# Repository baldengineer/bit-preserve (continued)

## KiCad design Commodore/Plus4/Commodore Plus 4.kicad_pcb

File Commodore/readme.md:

# Commodore
* VIC-20
  * [Assy 251027](https://github.com/baldengineer/bit-preserve/tree/master/Commodore/VIC-20)
* Plus4
  * [314001-04](https://github.com/baldengineer/bit-preserve/tree/master/Commodore/Plus4) (PCB 310162 Rev D)
* [C64](https://github.com/baldengineer/bit-preserve/tree/master/Commodore/C64)
  * [Schematic 251469](https://github.com/baldengineer/bit-preserve/tree/master/Commodore/C64/251469) (PCB 250425-01, 240441-01) 
* [C128](https://github.com/baldengineer/bit-preserve/tree/master/Commodore/C128)
  * [Assy 310378](https://github.com/baldengineer/bit-preserve/tree/master/Commodore/C128/310378)
* Peripherals
  * 1541 drive
    * [Assy 250446](https://github.com/baldengineer/bit-preserve/tree/master/Commodore/1541/250446)

# Wishlist
* PET
* C64
  * Schematic 326106 (PCB 326298-01)
  * Schematic 251022 (PCB KU-14194HB)
  * Schematic 251138 (PCB 250407-04)
* C64C
  * Schematic 252278 (PCB 250466)
  * Schematic 252312 (PCB 250469)
* C128D-CR
  * Schematic 252421 (PCB 250477-01)
* Peripherals
  * 1541-II drive

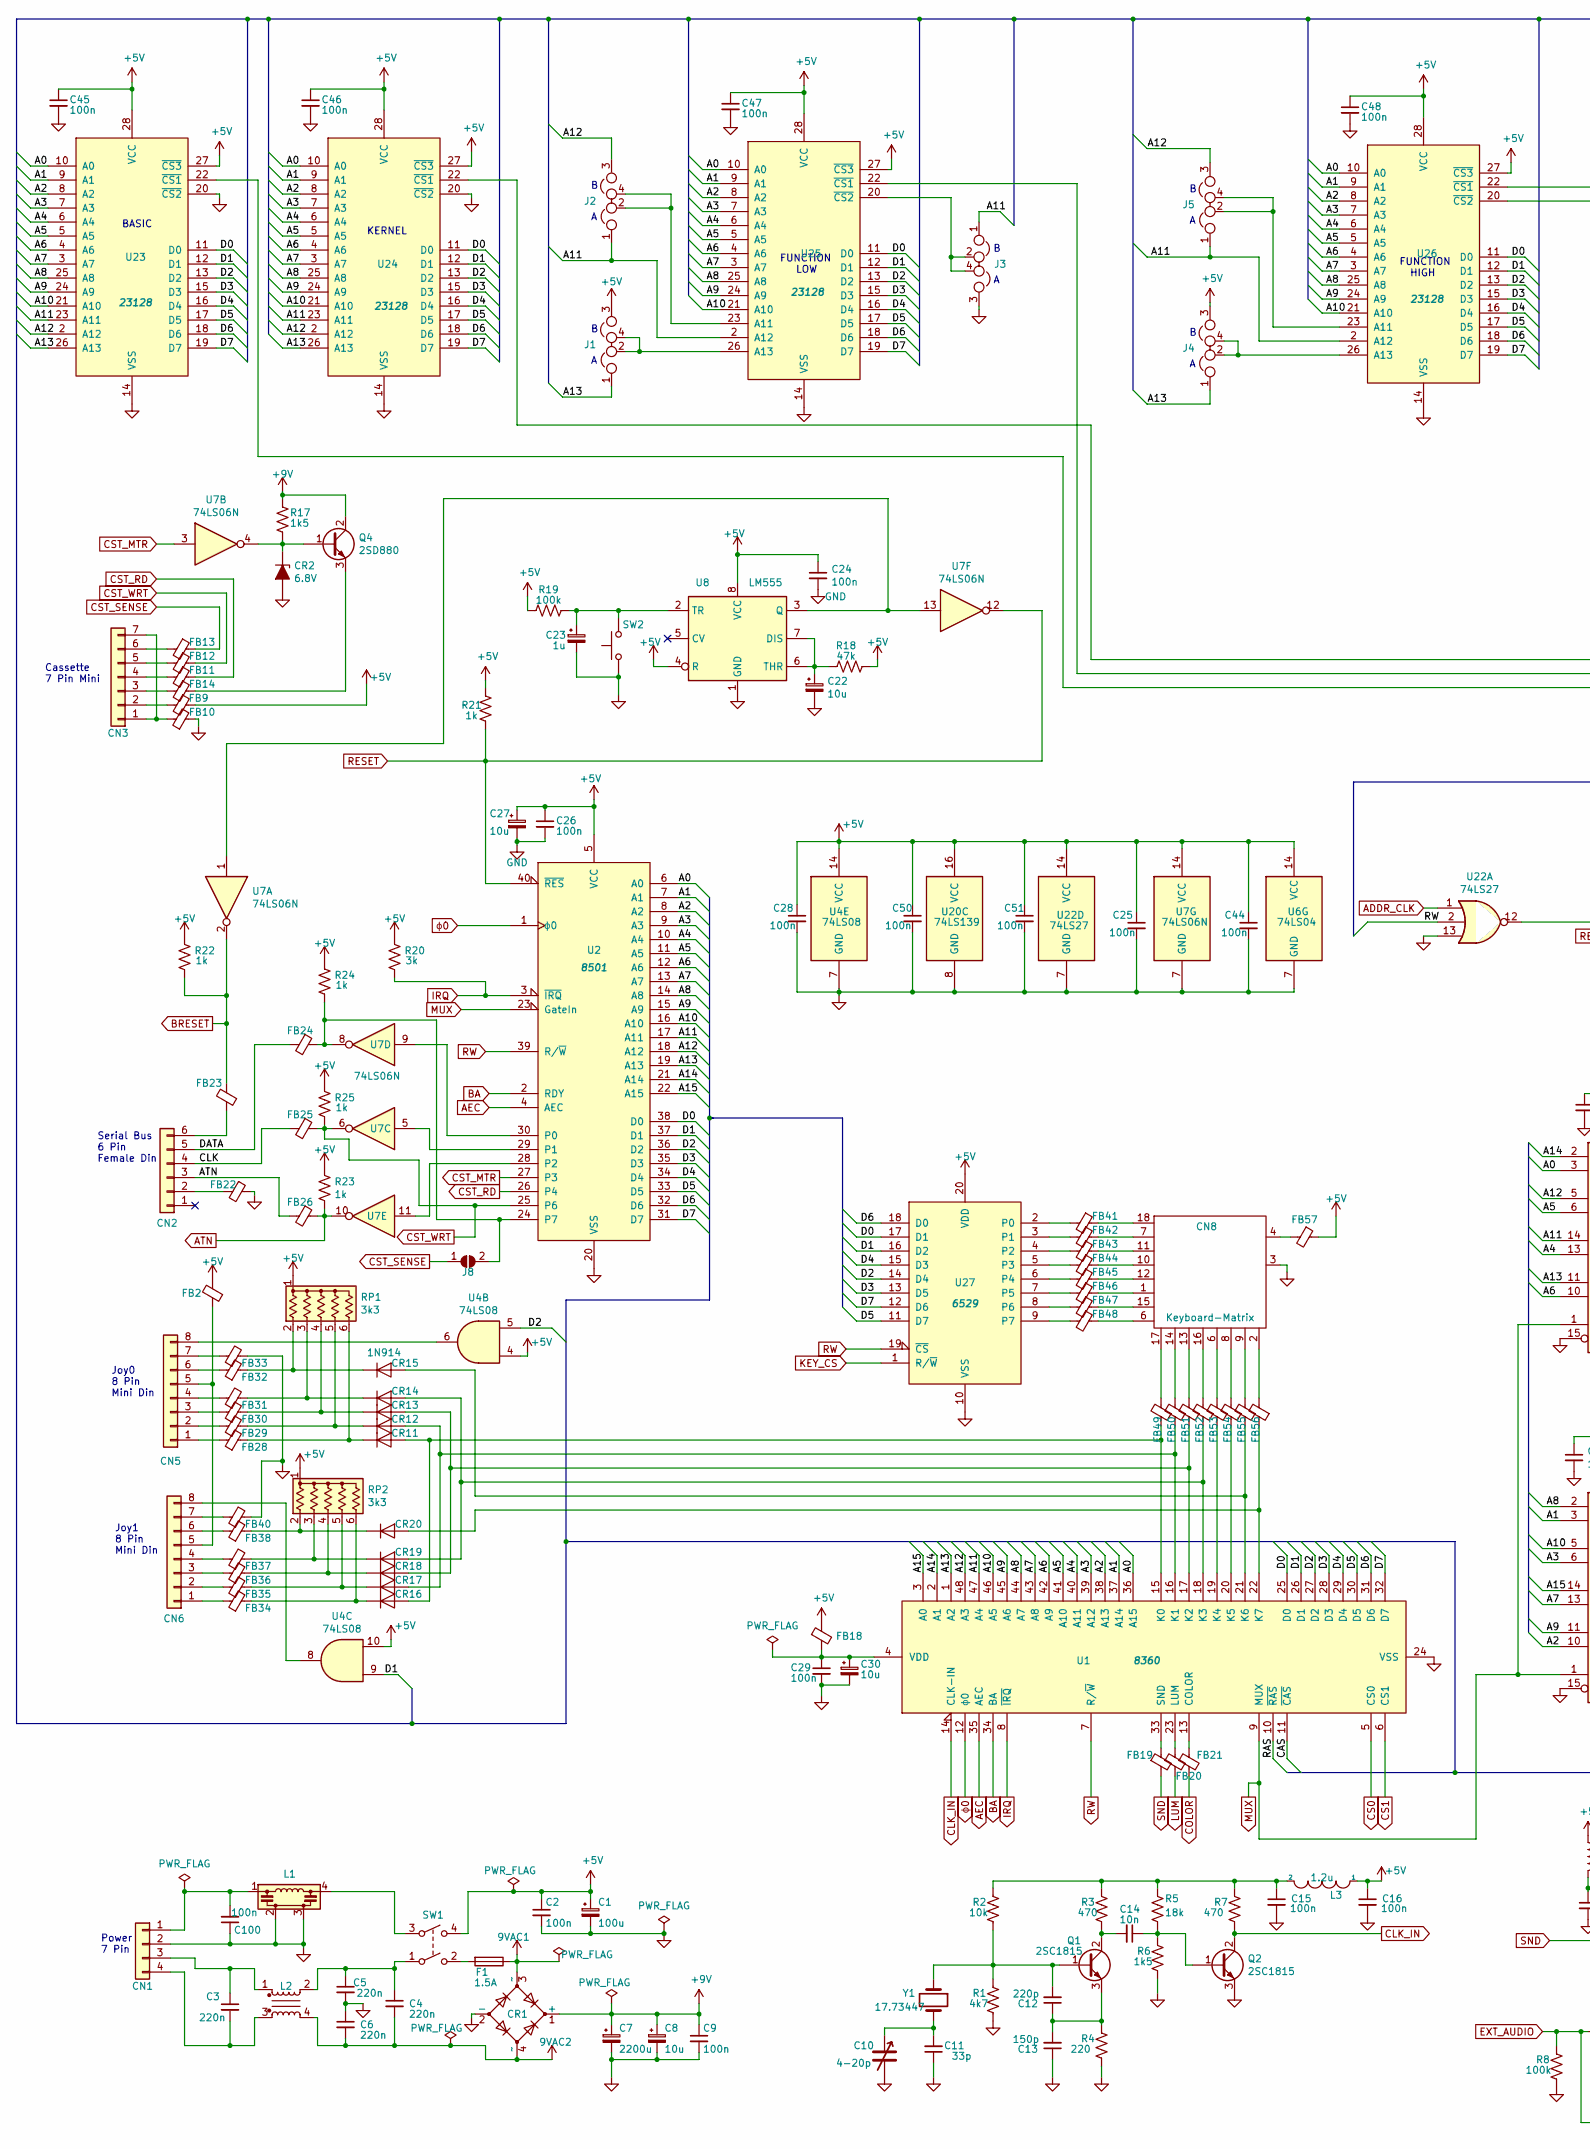
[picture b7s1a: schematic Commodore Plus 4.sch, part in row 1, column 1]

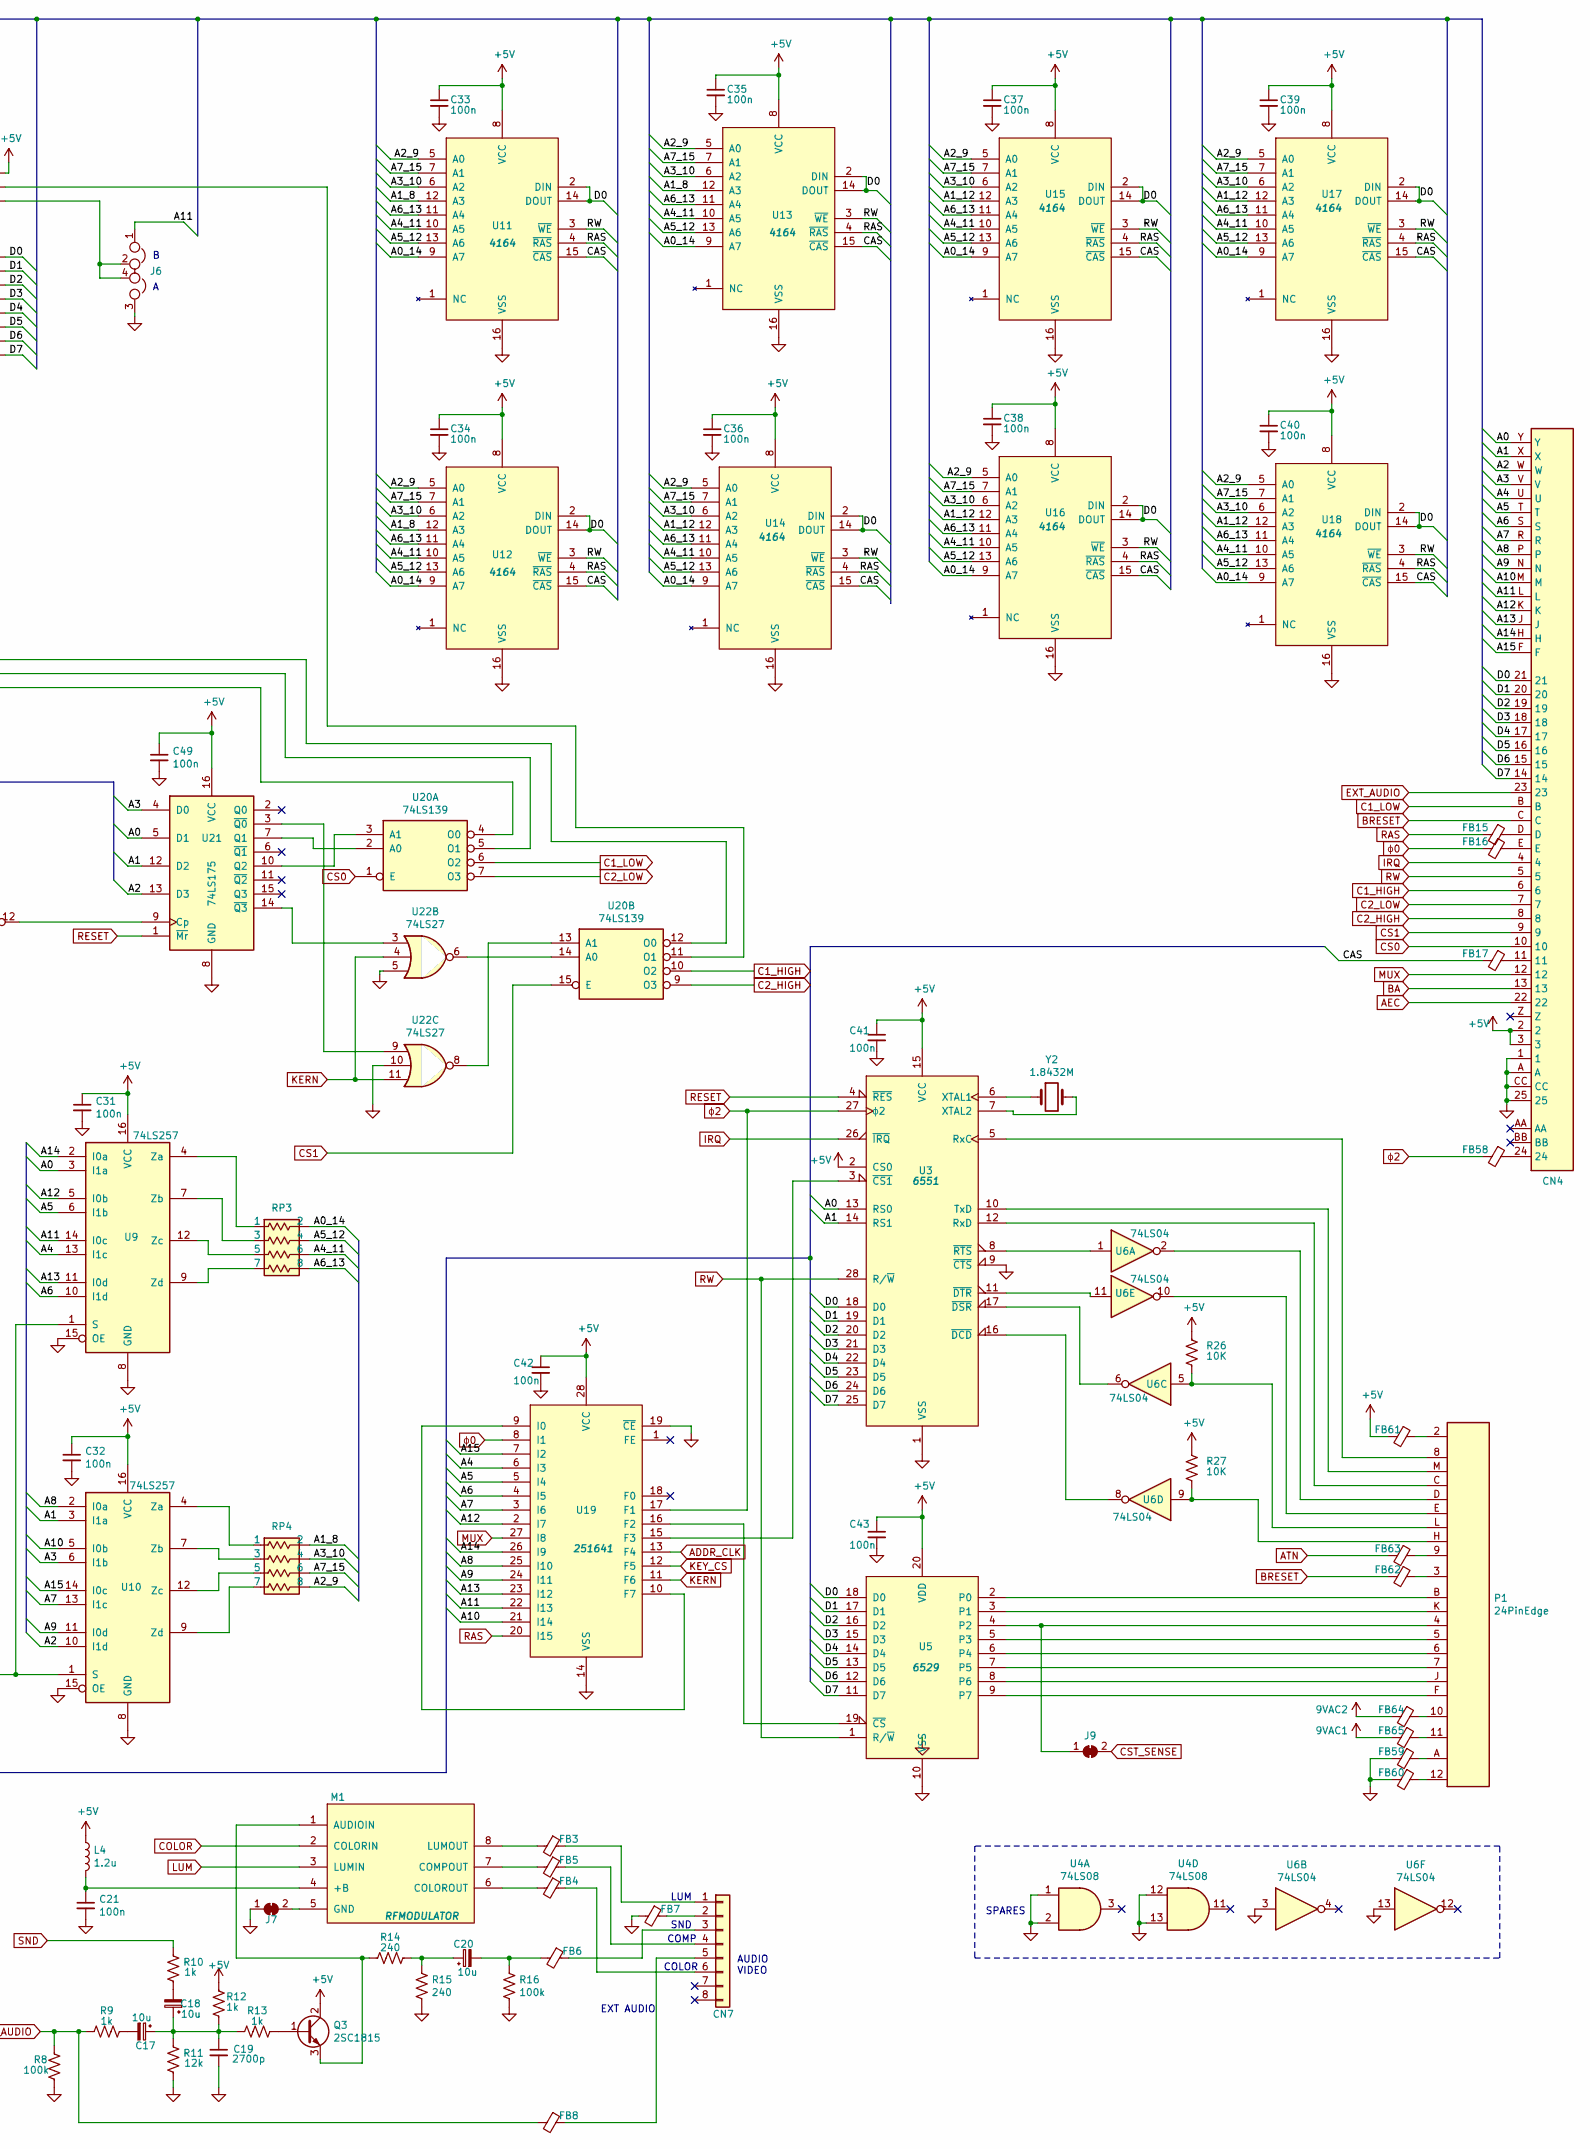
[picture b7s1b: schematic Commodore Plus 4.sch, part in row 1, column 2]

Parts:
C1: 100u; CP_Radial_D8.0mm_P3.50mm
C2, C9, C15, C16, C21, C24, C25, C26, C28, C29, C31, C32, C33, C34, C35, C36, C37, C38, C39, C41, C42, C43, C44, C45, C46, C47, C48, C49, C50, C51: 100n; C_Disc_D5.0mm_W2.5mm_P5.00mm
C3: 220n; C_Disc_D12.5mm_W5.0mm_P10.00mm
C4: 220n; Capacitor_D12.5mm_W5.0mm_P10.00mm
C5, C6: 220n; C_Disc_D5.0mm_W2.5mm_P5.00mm
C7: 2200u; CP_Axial_L40.0mm_D16.0mm_P48.00mm_Horizontal
C8, C20, C27: 10u; CP_Radial_D6.3mm_P2.50mm
C10: 4-20p; TrimCap_251029-02
C11: 33p; C_Disc_D5.0mm_W2.5mm_P5.00mm
C12: 220p; C_Disc_D5.0mm_W2.5mm_P5.00mm
C13: 150p; C_Disc_D5.0mm_W2.5mm_P5.00mm
C14: 10n; C_Disc_D5.0mm_W2.5mm_P5.00mm
C17, C18, C22, C30: 10u; C_Disc_10mm_6mm
C19: 2700p; C_Disc_D5.0mm_W2.5mm_P5.00mm
C23: 1u; CP_Radial_D6.3mm_P2.50mm
C40: 100n; C_Rect_L7.0mm_W2.5mm_P5.00mm
C100: 100n; C_Disc_D4.7mm_W2.5mm_P5.00mm
CN1: Conn_01x04; Connector_Power_4pin_251614_01
CN2: Conn_01x07; Connector_DIN_Female_6Pin_3rows
CN3: Conn_01x07; Connector_Mini-DIN_Female_7Pin_2rows
CN4: 50PinEdge; 50Pin_Edge_Connector
CN5, CN6: Conn_01x08; Connector_Mini-DIN_Female_8Pin_2rows
CN7: Conn_01x08; Connector_DIN_Female_8Pin_3rows
CN8: Keyboard-Matrix; Keyboard_Connector
CR1: D_Bridge_+-AA; Diode_Bridge_12.5x12.5
CR2: 6.8V; D_A-405_P12.70mm_Horizontal
CR11, CR12, CR13, CR14, CR15, CR16, CR17, CR18, CR19, CR20: 1N914; D_DO-35_SOD27_P12.70mm_Horizontal
F1: 1.5A; Fuseholder_Cylinder-6.3x32mm
FB2, FB3, FB4, FB5, FB6, FB7, FB8, FB9, FB10, FB11, FB12, FB13, FB14, FB22, FB23, FB24, FB25, FB26, FB28, FB29, FB30, FB31, FB32, FB33, FB34, FB35, FB36, FB37, FB38, FB40, FB59, FB61, FB62, FB63: Ferrite_Bead_Small; L_Axial_L7.0mm_D3.3mm_P5.08mm_Vertical
FB15, FB16, FB17, FB18, FB19, FB20, FB21, FB41, FB42, FB43, FB44, FB45, FB46, FB47, FB48, FB49, FB50, FB51, FB52, FB53, FB54, FB55, FB56, FB57, FB58, FB60, FB64, FB65: Ferrite_Bead_Small; Ferrite_Bead_L5.0mm_D3.6mm_P13.00mm_Horizontal
J1, J2, J3, J4, J5, J6: Jumper_NC_Dual; Jumper
J7, J9: SolderJumper_2_Bridged; SolderJumper-2_P1.3mm_Bridged_RoundedPad1.0x1.5mm
J8: SolderJumper_2_Open; SolderJumper-2_P1.3mm_Open_RoundedPad1.0x1.5mm
L1: EMI_Filter; EMI-Filter
L2: EMI_Filter_CommonMode; Noise_Filter
L3, L4: 1.2u; L_Axial_L10.0mm_D4.0mm_P15.5mm_Horizontal
M1: RFMODULATOR; RF_Modulator
P1: 24PinEdge; 24Pin_Edge
Q1, Q2, Q3: 2SC1815; TO-92L_Inline_Wide
Q4: 2SD880; TO-220-3_Vertical
R1: 4k7; Resistor_Horizontal
R2: 10k; Resistor_Horizontal
R3, R7: 470; Resistor_Horizontal
R4: 220; Resistor_Horizontal
R5: 18k; Resistor_Horizontal
R6, R17: 1k5; Resistor_Horizontal
R8, R16, R19: 100k; Resistor_Horizontal
R9, R10, R12, R13, R21, R22, R23, R24, R25: 1k; Resistor_Horizontal
R11: 12k; Resistor_Horizontal
R14, R15: 240; Resistor_Horizontal
R18: 47k; Resistor_Horizontal
R20: 3k; Resistor_Horizontal
R26, R27: 10K; Resistor_Horizontal
RP1, RP2: 3k3; R_Array_SIP6
RP3, RP4: Resistor-Network; R_Array_SIP8
SW1: SW_DPST; Switch-Rocker
SW2: SW_Push; Switch-Pushbutton
U1: 8360; DIP-48_W15.24mm
U2: 8501; DIP-40_W15.24mm
U3: 6551; DIP-28_W15.24mm
U4: 74LS08; DIP-14_W7.62mm
U5, U27: 6529; DIP-20_W7.62mm
U6: 74LS04; DIP-14_W7.62mm
U7: 74LS06N; DIP-14_W7.62mm
U8: LM555; DIP-8_W7.62mm
U9, U10: 74LS257; DIP-16_W7.62mm
U11, U12, U13, U14, U15, U16, U17, U18: 4164; DIP-16_W7.62mm
U19: 251641; DIP-28_W15.24mm
U20: 74LS139; DIP-16_W7.62mm
U21: 74LS175; DIP-16_W7.62mm
U22: 74LS27; DIP-14_W7.62mm
U23, U24, U25, U26: 23128; DIP-28_W15.24mm
Y1: 17.73447; Crystal_HC18-U_Horizontal
Y2: 1.8432M; Crystal_HC33-U_Horizontal

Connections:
9VAC1: CR1.3 (~~), F1.1, FB65.2
9VAC2: C4.2, C6.2, CR1.4 (~~), FB64.2, L2.4
+5V: C1.1, C2.1, C16.1, C24.1, C25.1, C26.1, C27.1, C28.1, C31.1, C32.1, C33.1, C34.1, C35.1, C36.1, C37.1, C38.1, C39.1, C40.1, C41.1, C42.1, C43.1, C44.1, C45.1, C46.1, C47.1, C48.1, C49.1, C50.1, C51.1, CN4.2, CN4.3, FB2.2, FB9.1, FB18.1, FB57.1, FB61.2, J1.3, J4.3, L3.1, L4.1, Q3.2 (C), R12.1, R18.1, R19.2, R20.1, R21.2, R22.1, R23.1, R24.1, R25.1, R26.1, R27.1, RP1.1 (common), RP2.1 (common), SW1.4, U2.5 (VCC), U3.2 (CS0), U3.15 (VCC), U4.4, U4.10, U4.14 (VCC), U5.20 (VDD), U6.14 (VCC), U7.14 (VCC), U8.4 (R), U8.8 (VCC), U9.16 (VCC), U10.16 (VCC), U11.8 (VCC), U12.8 (VCC), U13.8 (VCC), U14.8 (VCC), U15.8 (VCC), U16.8 (VCC), U17.8 (VCC), U18.8 (VCC), U19.28 (VCC), U20.16 (VCC), U21.16 (VCC), U22.14 (VCC), U23.27 (~CS3), U23.28 (VCC), U24.27 (~CS3), U24.28 (VCC), U25.27 (~CS3), U25.28 (VCC), U26.27 (~CS3), U26.28 (VCC), U27.20 (VDD)
+9V: C7.1, C8.1, C9.1, CR1.1 (+), Q4.2 (C), R17.1
/A0: CN4.Y, U1.36 (A15), U2.6 (A0), U3.13 (RS0), U9.3 (I1a), U21.5 (D1), U23.10 (A0), U24.10 (A0), U25.10 (A0), U26.10 (A0)
/A0_14: RP3.2, U11.9 (A7), U12.9 (A7), U13.9 (A7), U14.9 (A7), U15.9 (A7), U16.9 (A7), U17.9 (A7), U18.9 (A7)
/A1: CN4.X, U1.37 (A14), U2.7 (A1), U3.14 (RS1), U10.3 (I1a), U21.12 (D2), U23.9 (A1), U24.9 (A1), U25.9 (A1), U26.9 (A1)
/A1_8: RP4.2, U11.12 (A3), U12.12 (A3), U13.12 (A3)
/A1_12: U14.12 (A3), U15.12 (A3), U16.12 (A3), U17.12 (A3), U18.12 (A3)
/A2: CN4.W, U1.38 (A13), U2.8 (A2), U10.10 (I1d), U21.13 (D3), U23.8 (A2), U24.8 (A2), U25.8 (A2), U26.8 (A2)
/A2_9: RP4.8, U11.5 (A0), U12.5 (A0), U13.5 (A0), U14.5 (A0), U15.5 (A0), U16.5 (A0), U17.5 (A0), U18.5 (A0)
/A3: CN4.V, U1.39 (A12), U2.9 (A3), U10.6 (I1b), U21.4 (D0), U23.7 (A3), U24.7 (A3), U25.7 (A3), U26.7 (A3)
/A3_10: RP4.4, U11.6 (A2), U12.6 (A2), U13.6 (A2), U14.6 (A2), U15.6 (A2), U16.6 (A2), U17.6 (A2), U18.6 (A2)
/A4: CN4.U, U1.40 (A11), U2.10 (A4), U9.13 (I1c), U19.6 (I3), U23.6 (A4), U24.6 (A4), U25.6 (A4), U26.6 (A4)
/A4_11: RP3.6, U11.10 (A5), U12.10 (A5), U13.10 (A5), U14.10 (A5), U15.10 (A5), U16.10 (A5), U17.10 (A5), U18.10 (A5)
/A5: CN4.T, U1.41 (A10), U2.11 (A5), U9.6 (I1b), U19.5 (I4), U23.5 (A5), U24.5 (A5), U25.5 (A5), U26.5 (A5)
/A5_12: RP3.4, U11.13 (A6), U12.13 (A6), U13.13 (A6), U14.13 (A6), U15.13 (A6), U16.13 (A6), U17.13 (A6), U18.13 (A6)
/A6: CN4.S, U1.42 (A9), U2.12 (A6), U9.10 (I1d), U19.4 (I5), U23.4 (A6), U24.4 (A6), U25.4 (A6), U26.4 (A6)
/A6_13: RP3.8, U11.11 (A4), U12.11 (A4), U13.11 (A4), U14.11 (A4), U15.11 (A4), U16.11 (A4), U17.11 (A4), U18.11 (A4)
/A7: CN4.R, U1.43 (A8), U2.13 (A7), U10.13 (I1c), U19.3 (I6), U23.3 (A7), U24.3 (A7), U25.3 (A7), U26.3 (A7)
/A7_15: RP4.6, U11.7 (A1), U12.7 (A1), U13.7 (A1), U14.7 (A1), U15.7 (A1), U16.7 (A1), U17.7 (A1), U18.7 (A1)
/A8: CN4.P, U1.44 (A7), U2.14 (A8), U10.2 (I0a), U19.25 (I10), U23.25 (A8), U24.25 (A8), U25.25 (A8), U26.25 (A8)
/A9: CN4.N, U1.45 (A6), U2.15 (A9), U10.11 (I0d), U19.24 (I11), U23.24 (A9), U24.24 (A9), U25.24 (A9), U26.24 (A9)
/A10: CN4.M, U1.46 (A5), U2.16 (A10), U10.5 (I0b), U19.21 (I14), U23.21 (A10), U24.21 (A10), U25.21 (A10), U26.21 (A10)
/A11: CN4.L, J2.1, J3.1, J5.1, J6.1, U1.47 (A4), U2.17 (A11), U9.14 (I0c), U19.22 (I13), U23.23 (A11), U24.23 (A11), U25.2 (A12), U26.2 (A12)
/A12: CN4.K, J2.3, J5.3, U1.48 (A3), U2.18 (A12), U9.5 (I0b), U19.2 (I7), U23.2 (A12), U24.2 (A12)
/A13: CN4.J, J1.1, J4.1, U1.1 (A2), U2.19 (A13), U9.11 (I0d), U19.23 (I12), U23.26 (A13), U24.26 (A13)
/A14: CN4.H, U1.2 (A1), U2.21 (A14), U9.2 (I0a), U19.26 (I9)
/A15: CN4.F, U1.3 (A0), U2.22 (A15), U10.14 (I0c), U19.7 (I2)
/CAS: FB17.2, U1.11 (~CAS), U11.15 (~CAS), U12.15 (~CAS), U13.15 (~CAS), U14.15 (~CAS), U15.15 (~CAS), U16.15 (~CAS), U17.15 (~CAS), U18.15 (~CAS)
/CLK: CN2.4, FB25.2
/D0: CN4.21, U1.25 (D0), U2.38 (D0), U3.18 (D0), U5.18 (D0), U11.2 (DIN), U11.14 (DOUT), U12.2 (DIN), U12.14 (DOUT), U13.2 (DIN), U13.14 (DOUT), U14.2 (DIN), U14.14 (DOUT), U15.2 (DIN), U15.14 (DOUT), U16.2 (DIN), U16.14 (DOUT), U17.2 (DIN), U17.14 (DOUT), U18.2 (DIN), U18.14 (DOUT), U23.11 (D0), U24.11 (D0), U25.11 (D0), U26.11 (D0), U27.17 (D1)
/D1: CN4.20, U1.26 (D1), U2.37 (D1), U3.19 (D1), U4.9, U5.17 (D1), U23.12 (D1), U24.12 (D1), U25.12 (D1), U26.12 (D1), U27.16 (D2)
/D2: CN4.19, U1.27 (D2), U2.36 (D2), U3.20 (D2), U4.5, U5.16 (D2), U23.13 (D2), U24.13 (D2), U25.13 (D2), U26.13 (D2), U27.14 (D4)
/D3: CN4.18, U1.28 (D3), U2.35 (D3), U3.21 (D3), U5.15 (D3), U23.15 (D3), U24.15 (D3), U25.15 (D3), U26.15 (D3), U27.13 (D5)
/D4: CN4.17, U1.29 (D4), U2.34 (D4), U3.22 (D4), U5.14 (D4), U23.16 (D4), U24.16 (D4), U25.16 (D4), U26.16 (D4), U27.15 (D3)
/D5: CN4.16, U1.30 (D5), U2.33 (D5), U3.23 (D5), U5.13 (D5), U23.17 (D5), U24.17 (D5), U25.17 (D5), U26.17 (D5), U27.11 (D7)
/D6: CN4.15, U1.31 (D6), U2.32 (D6), U3.24 (D6), U5.12 (D6), U23.18 (D6), U24.18 (D6), U25.18 (D6), U26.18 (D6), U27.18 (D0)
/D7: CN4.14, U1.32 (D7), U2.31 (D7), U3.25 (D7), U5.11 (D7), U23.19 (D7), U24.19 (D7), U25.19 (D7), U26.19 (D7), U27.12 (D6)
/DATA: CN2.5, FB24.2
ADDR_CLK: U19.13 (F4), U22.1
AEC: CN4.22, U1.35 (AEC), U2.4 (AEC)
ATN: CN2.3, FB26.1, FB26.2, FB63.2, R23.2, U7.10
BA: CN4.13, U1.34 (BA), U2.2 (RDY)
BRESET: CN4.C, FB23.2, FB62.2, R22.2, U7.2
C1_HIGH: CN4.6, U20.10 (O2)
C1_LOW: CN4.B, U20.6 (O2)
C2_HIGH: CN4.8, U20.9 (O3)
C2_LOW: CN4.7, U20.7 (O3)
CLK_IN: Q2.2 (C), R7.2, U1.14 (CLK-IN)
COLOR: FB21.2, M1.2 (COLORIN)
CS0: CN4.10, U1.5 (CS0), U20.1 (E)
CS1: CN4.9, U1.6 (CS1), U20.15 (E)
CST_MTR: U2.27 (P3), U7.3
CST_RD: FB11.1, U2.26 (P4)
CST_SENSE: FB13.1, J8.1 (A), J9.2 (B)
CST_WRT: FB12.1, FB25.1, R25.2, U2.25 (P6), U7.6
EXT_AUDIO: CN4.23, FB8.2, R8.1, R9.2
GND: C1.2, C2.2, C5.2, C6.1, C7.2, C8.2, C9.2, C10.2, C11.1, C13.1, C15.2, C16.2, C19.2, C21.2, C22.2, C23.2, C24.2, C25.2, C26.2, C27.2, C28.2, C29.2, C30.2, C31.2, C32.2, C33.2, C34.2, C35.2, C36.2, C37.2, C38.2, C39.2, C40.2, C41.2, C42.2, C43.2, C44.2, C45.2, C46.2, C47.2, C48.2, C49.2, C50.2, C51.2, C100.1, CN1.2, CN4.1, CN4.25, CN4.A, CN4.CC, CN8.3, CR1.2 (-), CR2.2 (A), FB7.2, FB10.2, FB22.1, FB33.2, FB40.2, FB59.2, FB60.2, J3.3, J6.3, J7.1 (A), L1.2, L1.3, Q2.3 (E), R1.2, R4.2, R6.2, R8.2, R11.2, R15.2, R16.2, SW2.1, U1.24 (VSS), U2.20 (VSS), U3.1 (VSS), U3.9 (~CTS), U4.1, U4.2, U4.7 (GND), U4.12, U4.13, U5.10 (VSS), U6.3, U6.7 (GND), U6.13, U7.7 (GND), U8.1 (GND), U9.8 (GND), U9.15 (OE), U10.8 (GND), U10.15 (OE), U11.16 (VSS), U12.16 (VSS), U13.16 (VSS), U14.16 (VSS), U15.16 (VSS), U16.16 (VSS), U17.16 (VSS), U18.16 (VSS), U19.14 (VSS), U19.19 (~CE), U20.8 (GND), U21.8 (GND), U22.5, U22.7 (GND), U22.10, U22.13, U23.14 (VSS), U23.20 (~CS2), U24.14 (VSS), U24.20 (~CS2), U25.14 (VSS), U26.14 (VSS), U27.10 (VSS)
IRQ: CN4.4, R20.2, U1.8 (~IRQ), U2.3 (~IRQ), U3.26 (~IRQ)
KERN: U19.11 (F6), U22.4, U22.11
KEY_CS: U19.12 (F5), U27.1 (R/~W)
LUM: FB20.2, M1.3 (LUMIN)
MUX: CN4.12, U1.9 (MUX), U2.23 (GateIn), U9.1 (S), U10.1 (S), U19.27 (I8)
unnamed: C3.1, CN1.3, L2.1
unnamed: C3.2, CN1.4, L2.3
unnamed: C4.1, C5.1, L2.2, SW1.1
unnamed: C10.1, C11.2, Y1.2
unnamed: C12.1, C13.2, Q1.3 (E), R4.1
unnamed: C12.2, Q1.1 (B), R1.1, R2.2, Y1.1
unnamed: C14.1, Q2.1 (B), R5.2, R6.1
unnamed: C14.2, Q1.2 (C), R3.2
unnamed: C15.1, L3.2, R2.1, R3.1, R5.1, R7.1
unnamed: C17.1, C18.1, C19.1, R11.1, R12.2, R13.2
unnamed: C17.2, R9.1
unnamed: C18.2, R10.2
unnamed: C20.1, R14.1, R15.1
unnamed: C20.2, FB6.2, R16.1
unnamed: C21.1, L4.2, M1.4 (+B)
unnamed: C22.1, R18.2, U8.6 (THR), U8.7 (DIS)
unnamed: C23.1, R19.1, SW2.2, U8.2 (TR)
unnamed: C29.1, C30.1, FB18.2, U1.4 (VDD)
unnamed: C100.2, CN1.1, L1.1
unnamed: CN2.2, FB22.2
unnamed: CN2.6, FB23.1
unnamed: CN3.1, CN3.7, FB10.1
unnamed: CN3.2, FB9.2
unnamed: CN3.3, FB14.2
unnamed: CN3.4, FB11.2
unnamed: CN3.5, FB12.2
unnamed: CN3.6, FB13.2
unnamed: CN4.11, FB17.1
unnamed: CN4.24, FB58.1
unnamed: CN4.D, FB15.1
unnamed: CN4.E, FB16.1
unnamed: CN5.1, FB28.1
unnamed: CN5.2, FB29.1
unnamed: CN5.3, FB30.1
unnamed: CN5.4, FB31.1
unnamed: CN5.5, CN6.5, FB2.1
unnamed: CN5.6, FB32.1
unnamed: CN5.7, FB33.1
unnamed: CN5.8, U4.6
unnamed: CN6.1, FB34.1
unnamed: CN6.2, FB35.1
unnamed: CN6.3, FB36.1
unnamed: CN6.4, FB37.1
unnamed: CN6.6, FB38.1
unnamed: CN6.7, FB40.1
unnamed: CN6.8, U4.8
unnamed: CN7.1, FB3.1
unnamed: CN7.2, FB7.1
unnamed: CN7.3, FB6.1
unnamed: CN7.4, FB5.1
unnamed: CN7.5, FB8.1
unnamed: CN7.6, FB4.1
unnamed: CN8.1, FB46.1
unnamed: CN8.2, FB56.2
unnamed: CN8.4, FB57.2
unnamed: CN8.7, FB42.1
unnamed: CN8.8, FB54.2
unnamed: CN8.9, FB55.2
unnamed: CN8.10, FB44.1
unnamed: CN8.11, FB43.1
unnamed: CN8.12, FB45.1
unnamed: CN8.13, FB51.2
unnamed: CN8.14, FB50.2
unnamed: CN8.15, FB47.1
unnamed: CN8.16, FB52.2
unnamed: CN8.17, FB49.2
unnamed: CN8.18, FB41.1
unnamed: CR2.1 (K), Q4.1 (B), R17.2, U7.4
unnamed: CR11.1 (K), FB28.2, RP1.6 (R5)
unnamed: CR11.2 (A), CR16.2 (A), FB49.1, U1.15 (K0)
unnamed: CR12.1 (K), FB29.2, RP1.5 (R4)
unnamed: CR12.2 (A), CR17.2 (A), FB50.1, U1.16 (K1)
unnamed: CR13.1 (K), FB30.2, RP1.4 (R3)
unnamed: CR13.2 (A), CR18.2 (A), FB51.1, U1.17 (K2)
unnamed: CR14.1 (K), FB31.2, RP1.3 (R2)
unnamed: CR14.2 (A), CR19.2 (A), FB52.1, U1.18 (K3)
unnamed: CR15.1 (K), FB32.2, RP1.2 (R1)
unnamed: CR15.2 (A), FB55.1, U1.21 (K6)
unnamed: CR16.1 (K), FB34.2, RP2.6 (R5)
unnamed: CR17.1 (K), FB35.2, RP2.5 (R4)
unnamed: CR18.1 (K), FB36.2, RP2.4 (R3)
unnamed: CR19.1 (K), FB37.2, RP2.3 (R2)
unnamed: CR20.1 (K), FB38.2, RP2.2 (R1)
unnamed: CR20.2 (A), FB56.1, U1.22 (K7)
unnamed: F1.2, SW1.2
unnamed: FB3.2, M1.8 (LUMOUT)
unnamed: FB4.2, M1.6 (COLOROUT)
unnamed: FB5.2, M1.7 (COMPOUT)
unnamed: FB14.1, Q4.3 (E)
unnamed: FB19.1, U1.33 (SND)
unnamed: FB20.1, U1.23 (LUM)
unnamed: FB21.1, U1.13 (COLOR)
unnamed: FB24.1, J8.2 (B), R24.2, U2.24 (P7), U7.8
unnamed: FB41.2, U27.2 (P0)
unnamed: FB42.2, U27.3 (P1)
unnamed: FB43.2, U27.4 (P2)
unnamed: FB44.2, U27.5 (P3)
unnamed: FB45.2, U27.6 (P4)
unnamed: FB46.2, U27.7 (P5)
unnamed: FB47.2, U27.8 (P6)
unnamed: FB48.2, U27.9 (P7)
unnamed: FB53.1, U1.19 (K4)
unnamed: FB54.1, U1.20 (K5)
unnamed: FB59.1, P1.A
unnamed: FB60.1, P1.12
unnamed: FB61.1, P1.2
unnamed: FB62.1, P1.3
unnamed: FB63.1, P1.9
unnamed: FB64.1, P1.10
unnamed: FB65.1, P1.11
unnamed: J1.2, J1.4, U25.26 (A13)
unnamed: J2.2, J2.4, U25.23 (A11)
unnamed: J3.2, J3.4, U25.20 (~CS2)
unnamed: J4.2, J4.4, U26.26 (A13)
unnamed: J5.2, J5.4, U26.23 (A11)
unnamed: J6.2, J6.4, U26.20 (~CS2)
unnamed: J7.2 (B), M1.5 (GND)
unnamed: J9.1 (A), P1.4, U5.4 (P2)
unnamed: L1.4, SW1.3
unnamed: M1.1 (AUDIOIN), Q3.3 (E), R14.2
unnamed: P1.5, U5.5 (P3)
unnamed: P1.6, U5.6 (P4)
unnamed: P1.7, U5.7 (P5)
unnamed: P1.8, U3.5 (RxC)
unnamed: P1.B, U5.2 (P0)
unnamed: P1.C, U3.12 (RxD)
unnamed: P1.D, U6.2
unnamed: P1.E, U6.10
unnamed: P1.F, U5.9 (P7)
unnamed: P1.H, R27.2, U6.9
unnamed: P1.J, U5.8 (P6)
unnamed: P1.K, U5.3 (P1)
unnamed: P1.L, R26.2, U6.5
unnamed: P1.M, U3.10 (TxD)
unnamed: Q3.1 (B), R13.1
unnamed: RP3.1, U9.4 (Za)
unnamed: RP3.3, U9.7 (Zb)
unnamed: RP3.5, U9.12 (Zc)
unnamed: RP3.7, U9.9 (Zd)
unnamed: RP4.1, U10.4 (Za)
unnamed: RP4.3, U10.7 (Zb)
unnamed: RP4.5, U10.12 (Zc)
unnamed: RP4.7, U10.9 (Zd)
unnamed: U2.28 (P2), U7.11
unnamed: U2.29 (P1), U7.5
unnamed: U2.30 (P0), U7.9
unnamed: U3.6 (XTAL1), Y2.1
unnamed: U3.7 (XTAL2), Y2.2
unnamed: U3.8 (~RTS), U6.1
unnamed: U3.11 (~DTR), U6.11
unnamed: U3.16 (~DCD), U6.8
unnamed: U3.17 (~DSR), U6.6
unnamed: U7.1, U7.13, U8.3 (Q)
unnamed: U19.9 (I0), U19.10 (F7)
unnamed: U3.3 (~CS1), U19.15 (F3)
unnamed: U5.19 (~CS), U19.16 (F2)
unnamed: U20.2 (A0), U21.7 (Q1)
unnamed: U20.3 (A1), U21.10 (Q2)
unnamed: U20.4 (O0), U23.22 (~CS1)
unnamed: U20.5 (O1), U25.22 (~CS1)
unnamed: U20.11 (O1), U26.22 (~CS1)
unnamed: U20.12 (O0), U24.22 (~CS1)
unnamed: U20.13 (A1), U22.8
unnamed: U20.14 (A0), U22.6
unnamed: U21.3 (~Q0), U22.9
unnamed: U21.9 (Cp), U22.12
unnamed: U21.14 (~Q3), U22.3
RAS: FB15.2, U1.10 (~RAS), U11.4 (~RAS), U12.4 (~RAS), U13.4 (~RAS), U14.4 (~RAS), U15.4 (~RAS), U16.4 (~RAS), U17.4 (~RAS), U18.4 (~RAS), U19.20 (I15)
RESET: R21.1, U2.40 (~RES), U3.4 (~RES), U7.12, U21.1 (~Mr)
RW: CN4.5, U1.7 (R/~W), U2.39 (R/~W), U3.28 (R/~W), U5.1 (R/~W), U11.3 (~WE), U12.3 (~WE), U13.3 (~WE), U14.3 (~WE), U15.3 (~WE), U16.3 (~WE), U17.3 (~WE), U18.3 (~WE), U22.2, U27.19 (~CS)
SND: FB19.2, R10.1
ϕ0: FB16.2, U1.12 (ϕ0), U2.1 (ϕ0), U19.8 (I1)
ϕ2: FB58.2, U3.27 (ϕ2), U19.17 (F1)

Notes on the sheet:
BASIC
KERNEL
FUNCTION LOW
FUNCTION HIGH
Power 7 Pin
Serial Bus 6 Pin Female Din
Joy0 8 Pin Mini Din
Joy1 8 Pin Mini Din
LUM
SND
COMP
EXT AUDIO
COLOR
Cassette 7 Pin Mini
AUDIO VIDEO
SPARES

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
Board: 2 copper layers, 216 parts (0 on the bottom side), 238 nets, no tracks yet.

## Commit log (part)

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2019-08-05 Added value to clock trimcap
2019-08-05 Checked all stand-alone board resistors (except on RF modulator) in BOM against Service Manual parts list, and added rating and tolerance information from parts list to them - noted the following Rs 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
2019-08-06 Showing Power LED connection to LED connector
2019-08-07 added .gitignore for -bak files generated by Kicad
2019-08-07 checked all inductors (except RF mod.) in KiCad schematic BOM against Service Manual Parts List
2019-08-09 checked all diaodes (except in RF mod.) in KiCad schematic BOM against Service Manual parts list
2019-08-09 Added missing pull-ups on /EXROM and /GAME in cartridge expansion section (part of missing RP4 resistor network)
2019-08-09 Added missing R51 pull-up on R/W in cartridge expansion section
2019-08-09 checked SW1 abd F1 in KiCad schematic BOM against Service Manual parts list
2019-08-10 schematic revision/issue-date bump to 0.2/2019-08-11
2019-08-11 refac: Moved RP4 out of IO section to top-level sheet, as it's not really IO specific. Also fixed a bus connectivity issue with RP4 reported by ERC
2019-08-11 Replaced sym-lib-table absolute paths from initial submitter's file system with project relative paths, so that libs can be found when schematic is opened from other people's working copies
2019-08-13 Some part of the Terminal Section has been redrawn, no netlist changes
2019-09-24 Add Subfolder for computers by Dragon Data Ltd.
    Add basic KiCad project files for Dragon 32 computer
2019-09-27 Add MC6883/74LS783 chip
2019-09-27 Fix pin assginment on 74LS783/MC6883
2019-09-27 Add Dragon 32 BASIC ROM
2019-09-27 Add MC6847 symbol
2019-09-27 Fix GND assignment
2019-09-27 Add Siemens RAM Memory library
2020-01-01 Updated part names
2020-01-01 Added Decoupling Capacitor Page
    Need to verify.
2020-03-13 Schematics for Amiga A500 Power Supply
2020-04-19 Add C64B3 schematic
    This adds C= scheamtic #252278 which matches PCB #250466.
    It also adds TMS RAM 4464 in three speed version.
    MOS 8701 is updated to make pin 4 not hidden as it's
    usually connected to ground, not left floating.
2020-04-19 clarifying which number is used: assembly or board
2020-05-14 Captured digital/ICs for Sound page
    During live stream, captured the ICs on the sound page. Other page updates just because I opened the files to check status of the project.
2020-06-07 Video page
    Updated a few schematic symbols
2020-06-09 Adding CC-BY-SA License
2020-06-18 Worked on IWM Page
    Almost done with it! Thanks Stream!
2020-06-25 Finish IWM-4 Woo Hoo!
2020-07-19 Finished Sound Page (and the rest!)
    Cleaned up Capacitor page with polarized caps.
    Stil need to make some global labels (optional)
    Thank you chat! -> 2020-07-19
2020-08-22 Update readme.md
    Fixed formatting
2020-08-23 Started work on power supply
2020-08-25 Add CPU, video
2020-08-26 Complete video schematic
2020-10-14 Finish drawing initial version of Coco2 schematic
2020-10-15 Update Memory_Controller_Motorola.lib
    Change pin R/~W on MC6883 from output to input
2020-12-26 Fix CS1 signal on VIA1
2020-12-28 Pass 1 top row
    something weird happen, save me
2020-12-31 Horz, Vert, and PS ICs
    Streamed 2020-12-31
2021-01-03 Finish Schematic
2021-01-10 oops.
    Forgot to save when I committed.
2021-01-26 shematics for cpu, rom, io decode sheets halfway thru
2021-01-30 Updated RAM and RAM select sheets
2021-01-31 Added clock generator sheet, halfway thru it
2021-02-06 Update readme.md
    Added Apple II+ activity status.
2021-02-07 Additional updated to the Clock Generator Sheet, and the CPU sheet
2021-02-13 Added the CPU schematic
2021-02-14 Added video generation sheet
2021-02-15 Started to add footprints and vendor part numbers for BOM creation ordering ect... Started putting together power section.
2021-02-16 fixed the direction on some of the heirarichal pins
2021-02-18 -copied librares from troysbucket trs80 design and modified them -added DRAM schematic -started to put together SAM schematic.
2021-02-20 -Finished SAM sheet -Finsihed DRAM sheet
2021-02-21 added J6 connector ans started adding the video and periperals sheet
2021-02-21 Created separate II and II+ projects, stated updating the II+
2021-02-22 Updated Readme.md with more sources
2021-03-10 Schematic for BBC Micro PSU
2021-03-23 Added some more stuff to the perhipherals sheet
2021-03-23 Finished peripherals sheet. I think......
2021-03-24 -Finished schematic. -Cleaned up schematic. -Added final footprint. -Started PCB
2021-03-25 Fixed some footprints that had wrong number of pins.
2021-03-27 -Added more 3 models. -Improved alignment on some of the components.
2021-04-12 fixed unconnected traces
2021-04-13 added interactive BOM
2021-04-18 -added no fill zone around q1 -added part number for u4 pin socket -changed part number for c11 -modifed footprint for c43 -fixed value for c62 in schematic
2021-04-18 removed wayward no-connect
2021-04-20 added a revision number to the schematic and the pcb
2021-04-23 added Bill Of Materials BOM
2021-04-25 -cleaned up fab layer to display compoent values -updated gerbers and iBOM
2021-04-29 fixed 3d-model for din4 connector
2021-04-30 -Shortened the board by 1.5mm from the left side. -This should be the last change!!!
2021-05-03 added ground pads under cardedge connector
2021-05-11 added two more 3d models
2021-05-14 fixing amiga deleted file
2021-05-17 Clean-up after detailed circuit analysis - Fixed Reference to library in project file - Fixed BABUS tags on HCT245 (had wrong nets) - Flipped HCT245 circuits on MEGAII page to better match In/Out flo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
2021-06-03 Add page 1 schematic symbols
2021-06-04 Add page 2 symbols
    Does not include symbol for SA1, whatever that is.
2021-06-05 Additional page 2 symbols
2021-06-05 Add page 3 schematic symbols
2021-06-05 Rough top page routing
    Probably better if a lot of this is just net labels
2021-06-06 Label ASICs and other cleanup
2021-06-06 Page 3 layout tweaks
2021-06-06 Various corrections
2021-06-07 Added 7404 and 7438
2021-06-07 Snapshot of WIP, control and timing sheet done?
2021-06-09 Added 74125 and 74145
2021-06-09 Created lib for MOS Technology RAMs, added 2102 RAM (and aliases).
2021-06-09 Schematic capture complete, todo: verify against reference system.
2021-06-15 Fixed missing/wrong designators, keypad labeling between sheets, PA & PB routing between sheets.
2021-07-06 Initial commit for the schematic for the TRS-80 Color Computer 3 26-3334
2021-07-13 Updated component values.
2021-07-14 finished GIME section
2021-07-15 finished peripherals sheet
2021-07-16 added some more to the video sheet
2021-07-19 found and added lost capacitor c68
2021-07-19 changed paper type in video sheet
2021-07-31 -added some 3d models -fixed ferrite bead footprints
2021-08-04 adde symbol and footprint for the RF modulator
2021-08-05 added OSH logo
2021-08-06 started v2 updates on iigs-rom3
2021-08-10 moved some stuf around and rerouted some traces
2021-08-25 -Fixed R/W line not connected from the GIME to the CPU
2021-08-25 moved value to F silk
2021-08-30 Added a pull up resistor to SELA so that the new replacement PIA's are more compatible
2021-10-06 -Added DMA support by including a trace.It can be undone by cutting the normally closed side of the jumper and soldering the normally open -Added a normally open solder jumper to short out C62 if one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
2021-10-30 Updated readme and added pictures.
2022-01-01 added a space to the readme
2022-02-14 Update readme about PDFs
    Turns out, having a PDF to view on mobile devices would be nice. :)
2022-04-10 Updated to KiCad 6, created Readme
2022-04-16 updated components with readily available modern day components
2022-04-30 Corrected resistor values for R18..R23 and R41..R46 (transposed).
2022-07-09 added schematic and pcb design for the 26-313xA series of CoCo 2 motherboards
2022-09-20 Remove incomplete schematic
2022-10-24 Adding .zip to gitignore (to avoid backups)
2022-12-30 Apple II peripherals: add the EZCGI, a TMS9918A-based sprite graphics board
2023-01-27 kicad 6 and other updates
2023-01-28 802 ERC Errors
2023-01-28 Updated symbol library to v6
2023-01-28 moved v5 version to separate directory
2023-01-29 Formatting clean-up
2023-01-29 ROM3/KiCad v5 files cleanup
2023-01-29 moved rom3 pdf
2023-02-02 aded schematic and PCB layout for the 26-313xB Tandy Color COmputer 2 boards
2023-02-02 #82 replaced 28 MHz crystal with an oscillator symbol (and fixed pinout)
2023-02-03 Symbols for VA1 logic board
2023-02-05 Add bg fill to connectors. Modified VRAM to cleanly match ASIC. Matched major component designator to schematic. Added Buttons (sep sheet). Added modified GND symbols. Moved LCD to own sheet and rewo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
2023-02-06 Prepping for sound pre-amp to be added to LCD sheet
2023-02-07 Message anlaog stuff in LCD section. 100% right. Yup. It is. Except for the mistakes.
2023-02-07 inverter, audio buffer, and cleaned up various signals. A group of terms and fitlers for LCD need to be added.
2023-02-08 Colors for buses
2023-02-10 DC-DC converter (need to verify components)
2023-02-14 Saved for KiCad 7
2023-02-14 Game Gear v1 (VA1) PDFs
2023-02-17 initial commit for IIc
2023-02-18 TNG-EN resistor pack
2023-02-24 Capture sheet 2
2023-02-25 Aux RAM work. Need to wire to buffers.
2023-02-26 Created symbols KBD and IWM page
2023-02-26 finished iwm and keyboard page
2023-02-26 started serial page
2023-02-27 Fixed resistor packs
2023-02-27 Created Sound page (and moved sound elements to it) and added connectors sound and disks
2023-02-27 Re-arranging top sheet (and adding/removing signals from other blocks)
2023-02-28 Removed old sch files (after re-org)
2023-03-02 wired top level page, working through ERC and associated errors. Several errors related to matched outputs or inputs. Need to study actual IIc board to understand who drives what.
2023-03-04 ERC 4 error, 1 warning. these are tough issues to resolve. Not sure who generates what.
2023-03-10 fixed A14 on ROM and added note about ROM0 vs ROM3/4 boards
2023-05-05 added readme and changed name of pdf
2023-05-05 moved files to new dir
2023-05-05 KiCad 7 clean-up and ERC passes
2023-05-05 KiCad 7 initial start
2023-05-05 redrew 20-pin to match pysical pinout (odd-even)
2023-05-05 rev2: Added PDF and updated readme.
2023-09-21 initial v7 update commit
2023-09-22 Updated ICs with proper pin functions (except for VA1, whatever that is)
2023-09-22 Fixes #87
2023-09-28 minor IIgs fixes
2023-09-29 Fixed ERC issues and coverted to V7, changed PDF
2023-09-29 Initial open it as v7
2023-09-29 Started off-grid clean-up, 1900 to go!
2023-10-06 cleaned most off-grid warnings
2023-10-20 Started moving Global labels to Hierarchical and Local labels
2023-11-17 Fixed CAS and A6 on RAM page (plus lots of other clean ups)
2023-12-15 Changed SOFT5-A2-8 and -11 to just SOFT5, based on Apple II Circuit Description Book
2023-12-15 V1 PDF
2023-12-29 moving T3
2024-01-05 Created T2 and drew in its connections.
2024-01-12 created v1 pdf
2024-01-12 fixed #125, F12 had the wrong address range listed and re-generated PDF
2024-02-01 now 3d files too
2024-02-02 ignoring sym-lib-table
2024-02-09 continued work
2024-02-29 project readme update
2024-02-29 updated MC10 KiCad version note
2024-03-08 Added Modulator Unit and started ERC checks (gah)
2024-03-15 created CPU, ROM, two logic chips, and started gate array
2024-03-22 most of the analog board is done.
2024-04-01 finalized SE anlaog board, generated PDF, and created README
2024-04-01 created macintosh readme
2024-04-04 pre-done finished stage before ERC
2024-04-04 fixed XTAL2
2024-04-05 chagned pin map to ignore warnings on tri-state
2024-04-05 erc clean
2024-04-05 Update TRS readme.md
    added links
2025-02-06 Initial Save to KiCad 8
